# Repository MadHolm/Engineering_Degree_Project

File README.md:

# Engineer's Degree Project

# Soundfollowing Robot

Files include thesis, parts design, PCB design and Arduino-based software.

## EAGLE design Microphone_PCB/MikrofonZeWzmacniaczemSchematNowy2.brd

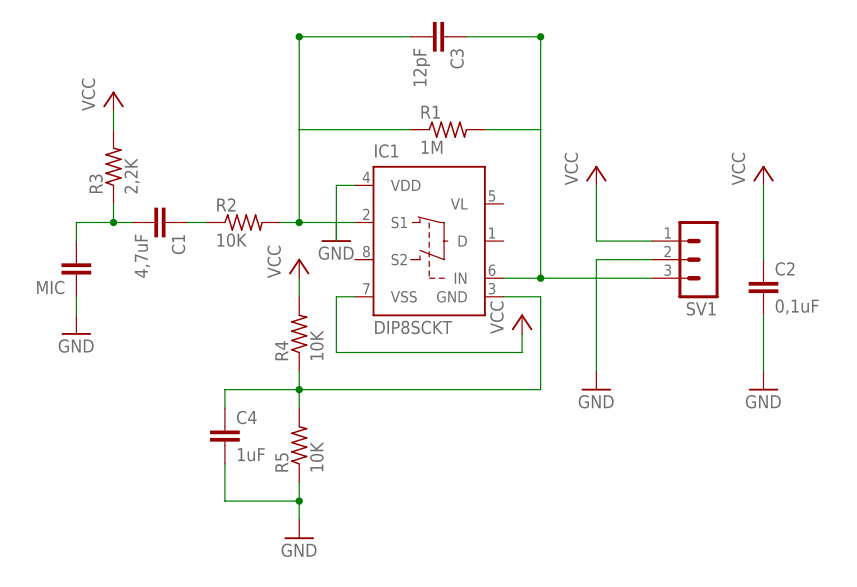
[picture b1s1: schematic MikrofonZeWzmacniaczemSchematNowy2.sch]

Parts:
C1: 4,7uF; C0805
C2: 0,1uF; C0805
C3: 12pF; C0805
C4: 1uF; C0805
IC1: DIP8SCKT; DIL08; MPN DIP8SOCKET
MIC: C2.5/6; C2.5-6
R1: 1M; R0805
R2, R4, R5: 10K; R0805
R3: 2,2K; R0805
SV1: MA03-1

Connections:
GND: C2.2, C4.2, IC1.4 (VDD), MIC.1, R5.1, SV1.2
unnamed: C3.2, IC1.2 (S1), R1.1, R2.2
unnamed: C3.1, IC1.6 (IN), R1.2, SV1.3
unnamed: C4.1, IC1.3 (GND), R4.1, R5.2
unnamed: C1.1, R2.1
unnamed: C1.2, MIC.2, R3.1
VCC: C2.1, IC1.7 (VSS), R3.2, R4.2, SV1.1
VL: IC1.5 (VL)

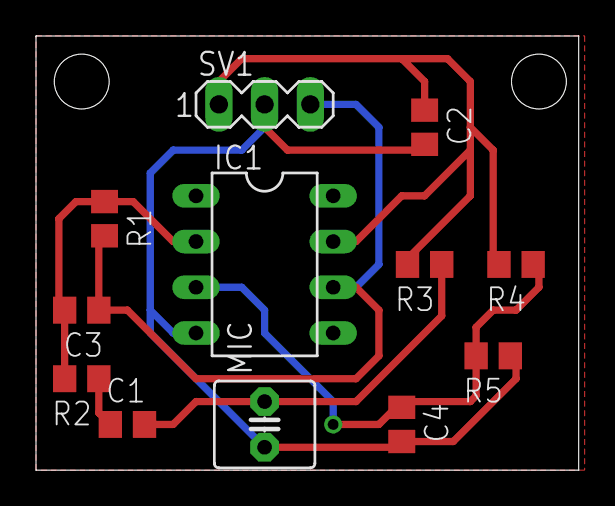
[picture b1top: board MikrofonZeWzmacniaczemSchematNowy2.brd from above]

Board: 2 copper layers, 30.1 x 24.1 mm, 12 parts (0 on the bottom side), 7 nets.

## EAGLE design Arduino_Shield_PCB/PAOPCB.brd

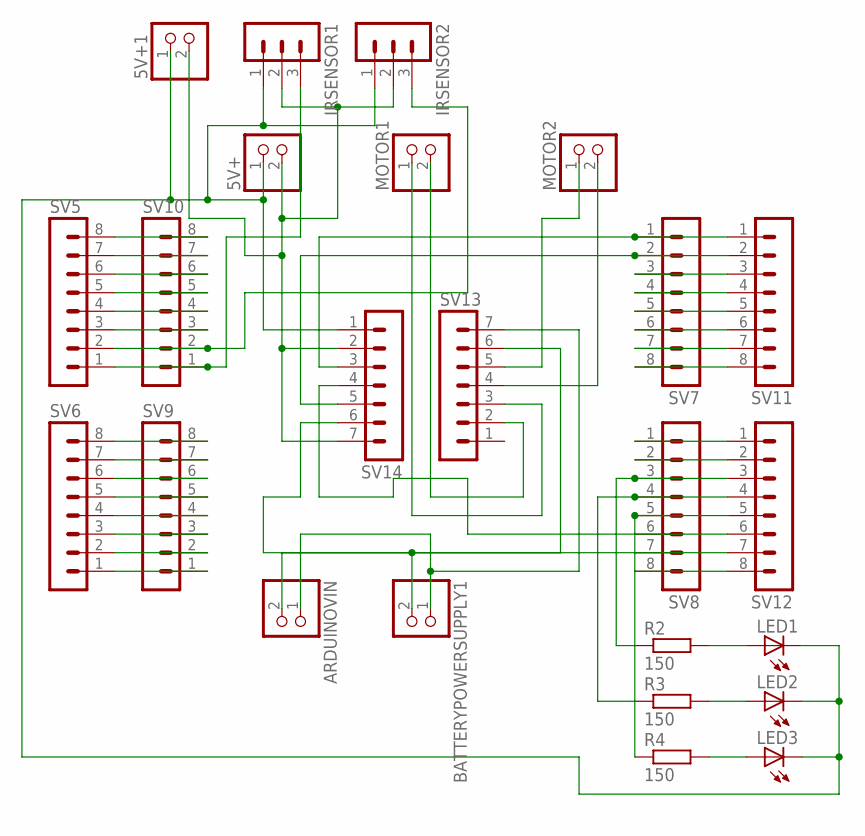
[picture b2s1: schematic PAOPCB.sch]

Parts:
5V+, 5V+1: PINHD-1X2; 1X02
ARDUINOVIN: PINHD-1X2; 1X02
BATTERYPOWERSUPPLY1: PINHD-1X2; 1X02
IRSENSOR1, IRSENSOR2: MA03-1
LED1, LED2, LED3: LEDSML0805; SML0805
MOTOR1, MOTOR2: PINHD-1X2; 1X02
R2, R3, R4: 150; M0805
SV5, SV6, SV7, SV8, SV9, SV10, SV11, SV12: MA08-1
SV13, SV14: MA07-1

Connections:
unnamed: 5V+.1, 5V+1.1, IRSENSOR1.1, IRSENSOR2.1, LED1.C, LED2.C, LED3.C, SV14.1
unnamed: LED1.A, R2.2
unnamed: LED2.A, R3.2
unnamed: LED3.A, R4.2
unnamed: ARDUINOVIN.1, BATTERYPOWERSUPPLY1.1, SV13.7
unnamed: SV8.1, SV12.1
unnamed: SV8.6, SV12.6, SV14.4
unnamed: SV5.8, SV10.8
unnamed: SV5.7, SV10.7
unnamed: SV5.6, SV10.6
unnamed: SV5.5, SV10.5
unnamed: SV5.4, SV10.4
unnamed: SV5.3, SV10.3
unnamed: IRSENSOR2.3, SV5.2, SV10.2
unnamed: IRSENSOR1.3, SV5.1, SV10.1
unnamed: SV6.8, SV9.8
unnamed: SV6.7, SV9.7
unnamed: SV6.6, SV9.6
unnamed: SV6.5, SV9.5
unnamed: SV6.4, SV9.4
unnamed: SV6.3, SV9.3
unnamed: SV6.2, SV9.2
unnamed: SV6.1, SV9.1
unnamed: SV7.1, SV11.1, SV14.3
unnamed: SV7.2, SV11.2, SV14.5
unnamed: SV7.3, SV11.3
unnamed: SV7.4, SV11.4
unnamed: SV7.5, SV11.5
unnamed: SV7.6, SV11.6
unnamed: SV7.7, SV11.7
unnamed: SV7.8, SV11.8
unnamed: SV8.7, SV12.7, SV14.6
unnamed: SV8.2, SV12.2
unnamed: R2.1, SV8.3, SV12.3
unnamed: R3.1, SV8.4, SV12.4
unnamed: R4.1, SV8.5, SV12.5
unnamed: SV8.8, SV12.8
unnamed: ARDUINOVIN.2, BATTERYPOWERSUPPLY1.2, SV13.6
unnamed: MOTOR2.1, SV13.5
unnamed: MOTOR2.2, SV13.4
unnamed: MOTOR1.1, SV13.3
unnamed: MOTOR1.2, SV13.2
unnamed: 5V+.2, 5V+1.2, IRSENSOR1.2, IRSENSOR2.2, SV14.2, SV14.7

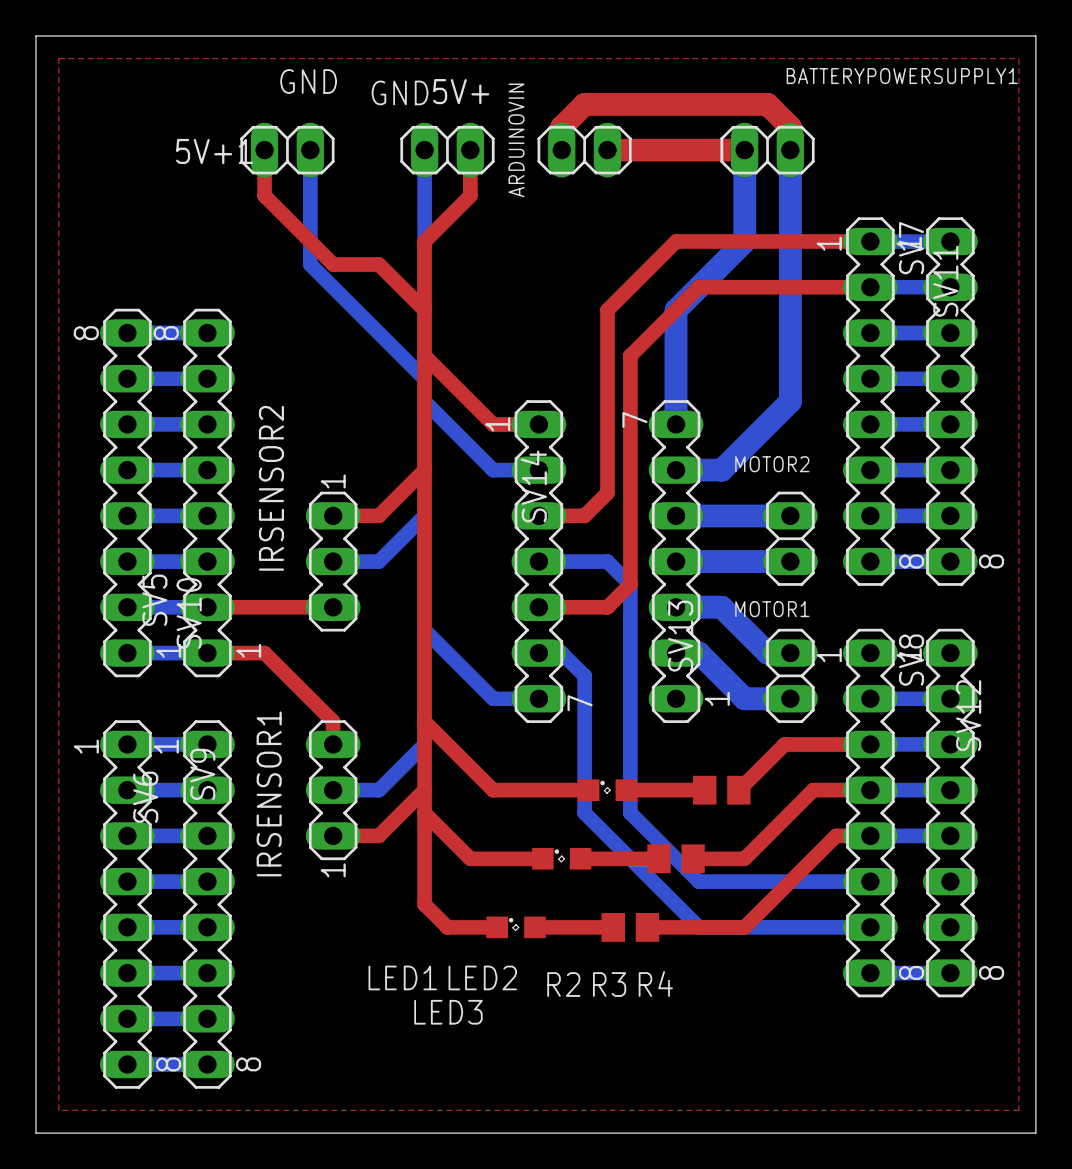
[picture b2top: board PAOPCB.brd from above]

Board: 2 copper layers, 55.5 x 61.0 mm, 24 parts (0 on the bottom side), 43 nets.

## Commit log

2018-09-10 All files regarding the engineering project
